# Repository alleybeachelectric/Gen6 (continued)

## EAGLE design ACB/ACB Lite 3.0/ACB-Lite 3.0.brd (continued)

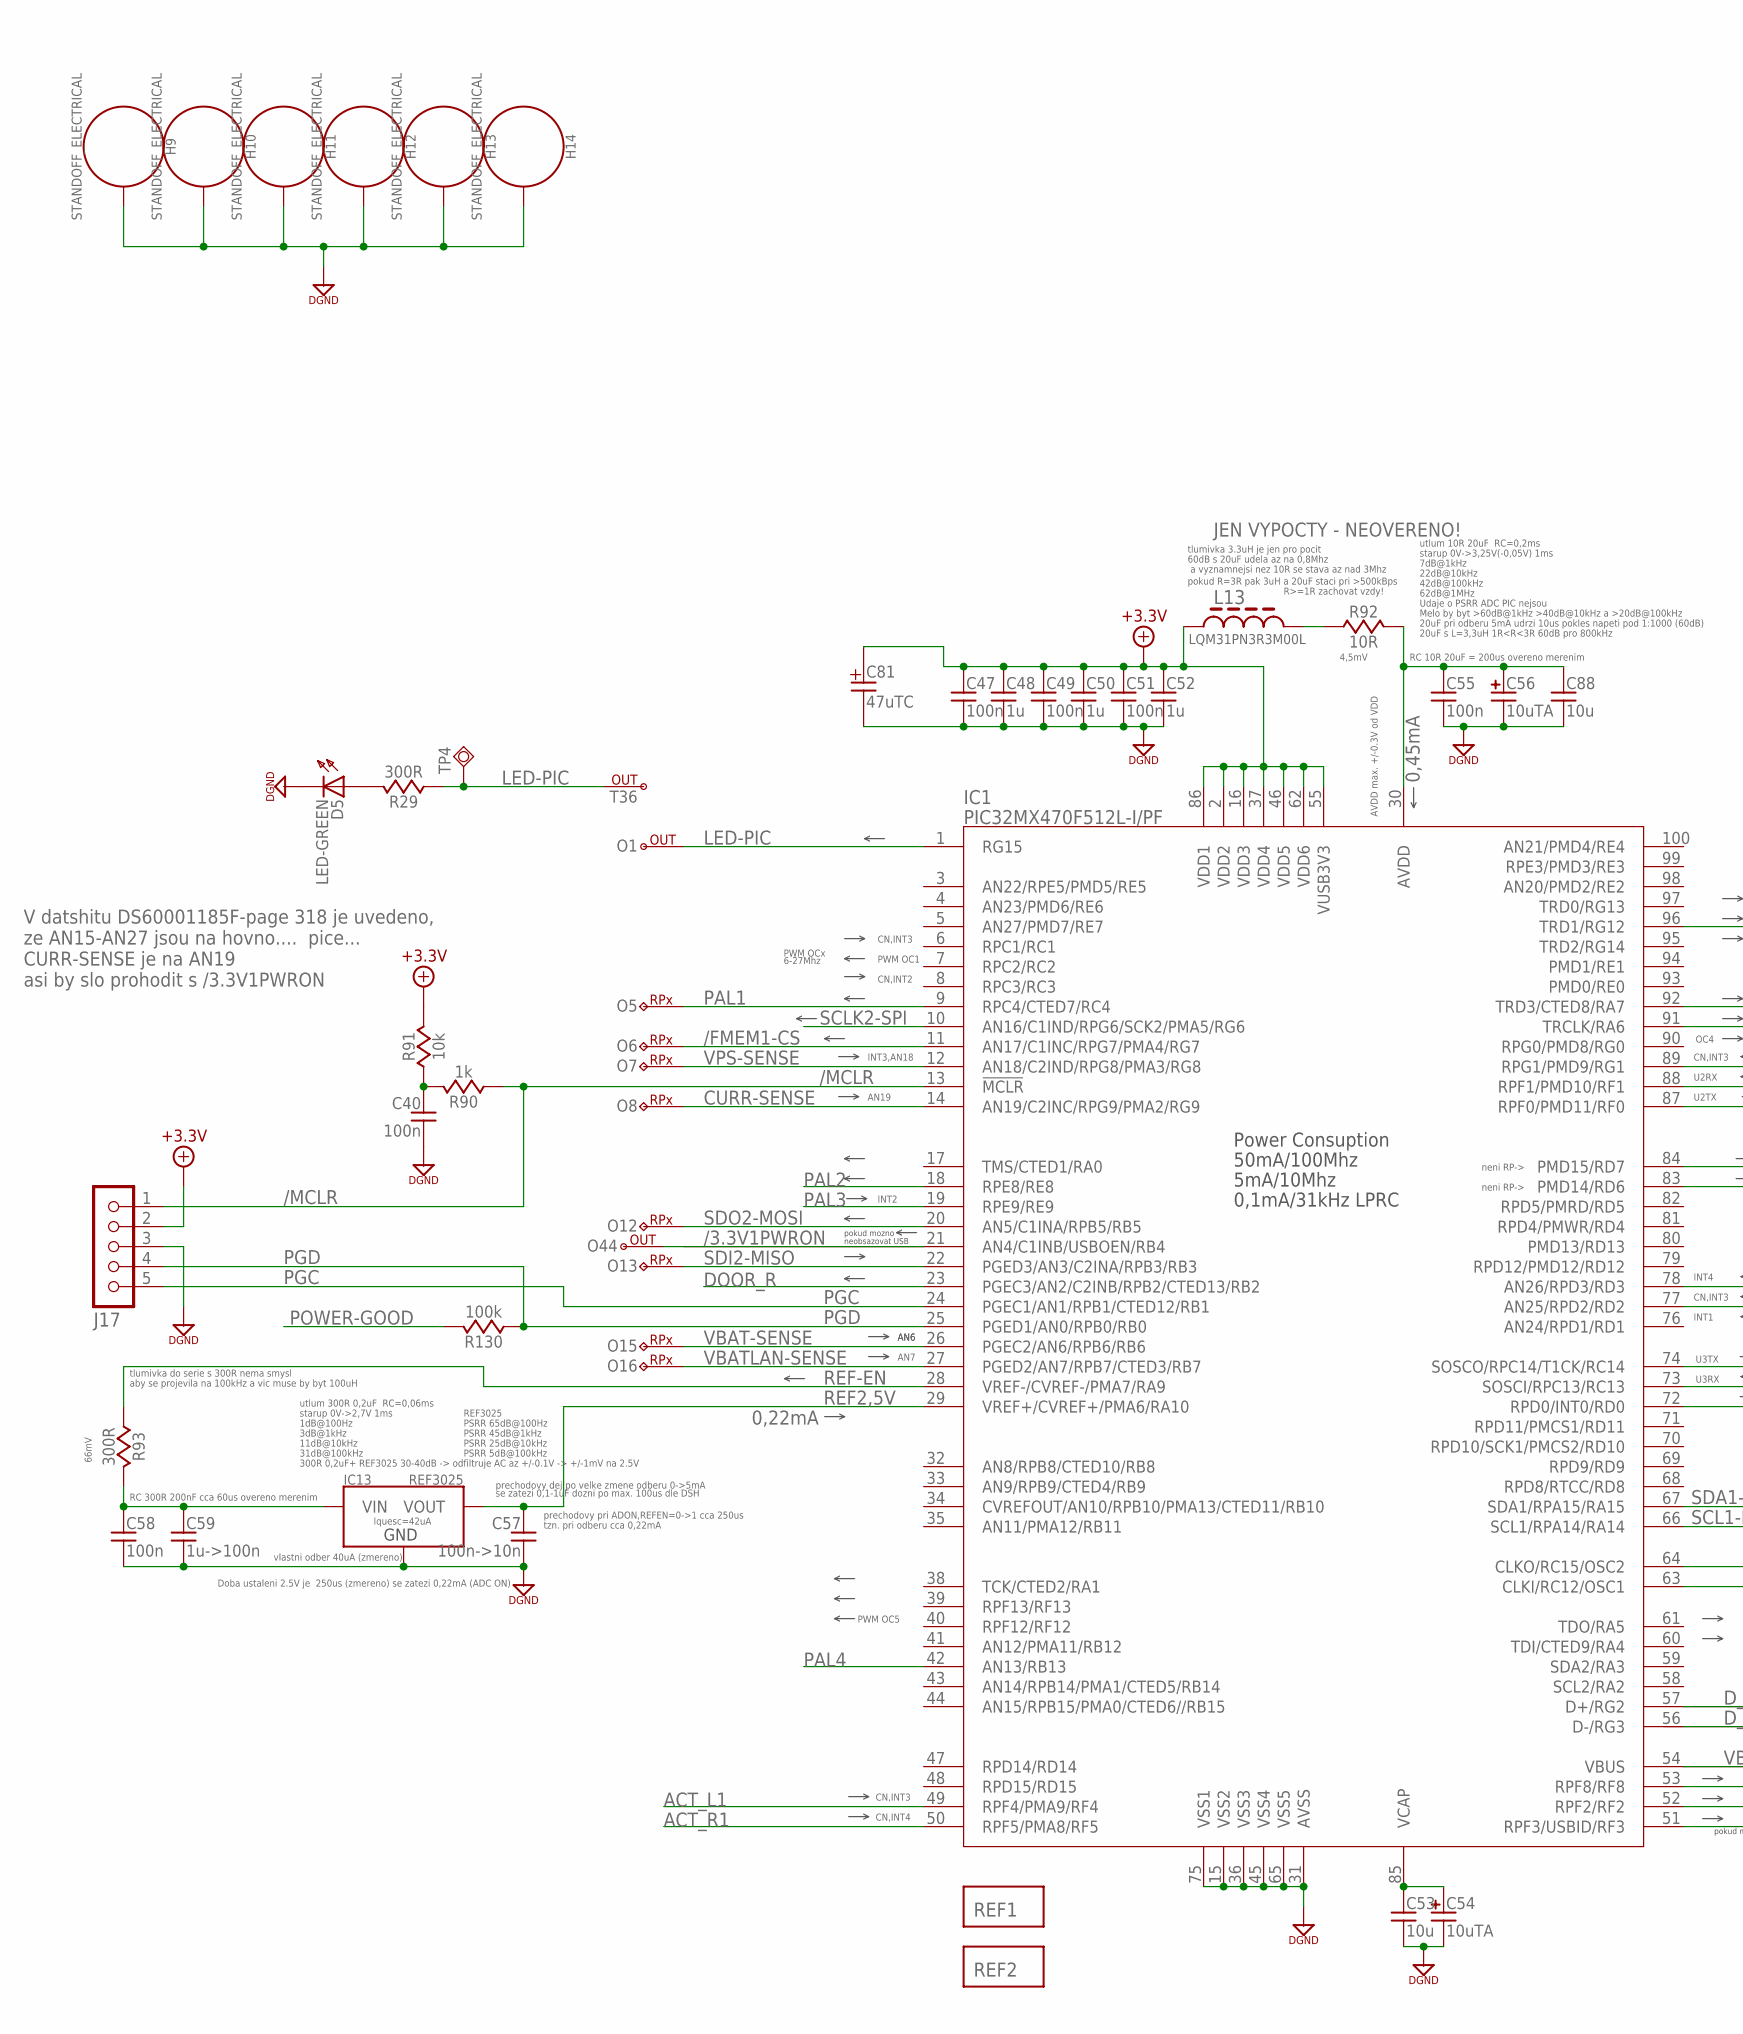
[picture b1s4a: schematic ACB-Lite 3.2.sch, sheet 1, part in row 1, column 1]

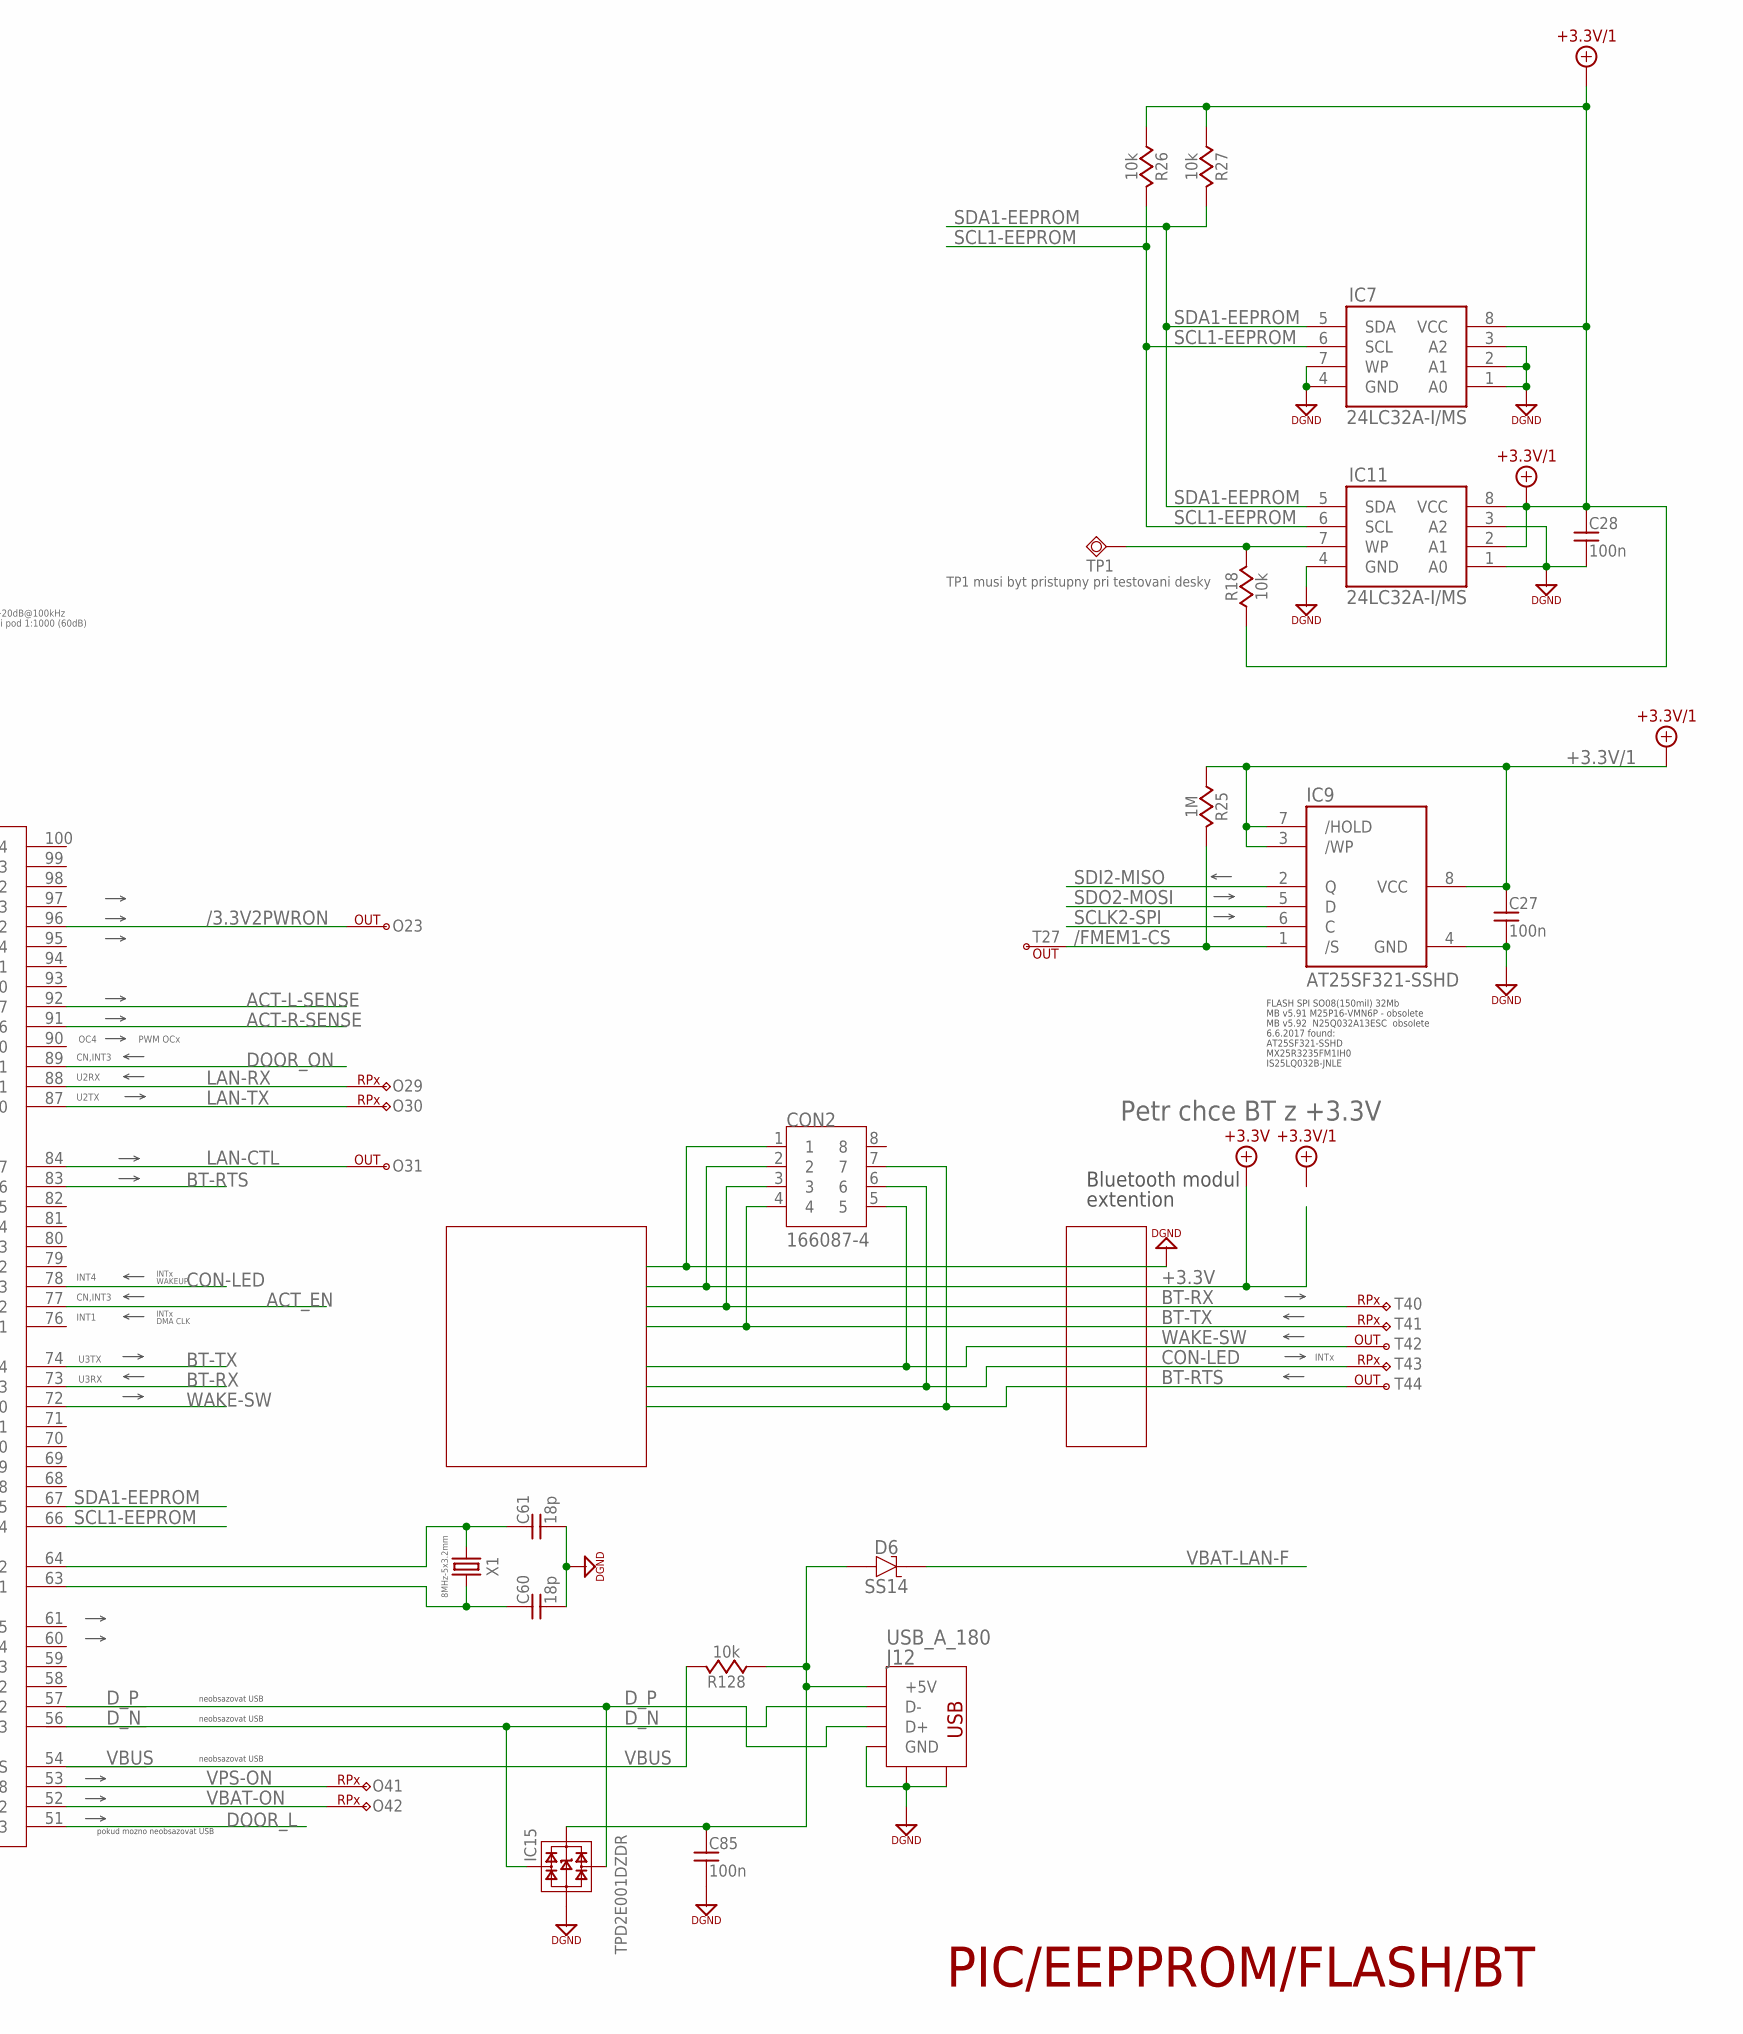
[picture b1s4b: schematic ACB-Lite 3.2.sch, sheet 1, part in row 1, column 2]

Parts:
C27, C28, C40, C47, C49, C51, C55, C58, C85: 100n; 0603
C48, C50, C52: 1u; 0603
C53, C88: 10u; 0603
C54, C56: 10uTA; 1206-POL-C
C57: 100n->10n; 0603
C59: 1u->100n; 0603
C60, C61: 18p; 0603
C81: 47uTC; CT-C
CON2: 166087-4
D5: LED-GREEN; 0805-POL-D
D6: SS14; SMA
H9, H10, H11, H12, H13, H14: STANDOFF_ELECTRICAL; STANDOFF-ELECTRICAL
IC1: PIC32MX470F512L-I/PF; TQFP100_14X14_0,5MM
IC7, IC11: 24LC32A-I/MS; MSOP-08
IC9: AT25SF321-SSHD; SO-08
IC13: REF3025; SOT23
IC15: TPD2E001DZDR; SOT-143
J12: USB_A_180; USB_B_180
J17: DNP-open-hole; MA05-1
L13: LQM31PN3R3M00L; 1206
O1, O23, O31, O44: PIC-OUT; TEMP-PAD
O5, O6, O7, O8, O12, O13, O15, O16, O29, O30, O41, O42: PIC-RPX; TEMP-PAD
R18, R26, R27, R91, R128: 10k; 0603
R25: 1M; 0603
R29, R93: 300R; 0603
R90: 1k; 0603
R92: 10R; 0603
R130: 100k; 0603
REF1, REF2: REF
T27, T36, T42, T44: PIC-OUT; TEMP-PAD
T40, T41, T43: PIC-RPX; TEMP-PAD
TP1: DNP-TestPoint; SMD_ROUND_1MM
TP4: DNP-TestPoint; TH_ROUND_14MM08MM
X1: 8MHz-5x3.2mm; 7B

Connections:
+3.3V: C47.1, C48.1, C49.1, C50.1, C51.1, C52.1, C81.+, CON2.2, IC1.2 (VDD2), IC1.16 (VDD3), IC1.37 (VDD4), IC1.46 (VDD5), IC1.55 (VUSB3V3), IC1.62 (VDD6), IC1.86 (VDD1), J17.2, L13.1, R91.2; also elsewhere on the board
+3.3V/1: C27.1, C28.1, IC7.8 (VCC), IC9.3 (/WP), IC9.7 (/HOLD), IC9.8 (VCC), IC11.2 (A1), IC11.8 (VCC), R18.1, R25.2, R26.1, R27.1; also elsewhere on the board
/3.3V1PWRON: IC1.21 (AN4/C1INB/USBOEN/RB4), O44.P$1; also elsewhere on the board
/3.3V2PWRON: IC1.96 (TRD1/RG12), O23.P$1; also elsewhere on the board
/FMEM1-CS: IC1.11 (AN17/C1INC/RPG7/PMA4/RG7), IC9.1 (/S), O6.P$1, R25.1, T27.P$1
/MCLR: IC1.13 (!MCLR), J17.1, R90.2
ACT-L-SENSE: IC1.92 (TRD3/CTED8/RA7); also elsewhere on the board
ACT-R-SENSE: IC1.91 (TRCLK/RA6); also elsewhere on the board
ACT_EN: IC1.77 (AN25/RPD2/RD2); also elsewhere on the board
ACT_L1: IC1.49 (RPF4/PMA9/RF4); also elsewhere on the board
ACT_R1: IC1.50 (RPF5/PMA8/RF5); also elsewhere on the board
AVDD: C55.1, C56.+, C88.1, IC1.30 (AVDD), R92.2
BT-RTS: CON2.7, IC1.83 (PMD14/RD6), T44.P$1; also elsewhere on the board
BT-RX: CON2.3, IC1.73 (SOSCI/RPC13/RC13), T40.P$1; also elsewhere on the board
BT-TX: CON2.4, IC1.74 (SOSCO/RPC14/T1CK/RC14), T41.P$1; also elsewhere on the board
CON-LED: CON2.6, IC1.78 (AN26/RPD3/RD3), T43.P$1; also elsewhere on the board
CURR-SENSE: IC1.14 (AN19/C2INC/RPG9/PMA2/RG9), O8.P$1; also elsewhere on the board
DOOR_L: IC1.51 (RPF3/USBID/RF3); also elsewhere on the board
DOOR_ON: IC1.89 (RPG1/PMD9/RG1); also elsewhere on the board
DOOR_R: IC1.23 (PGEC3/AN2/C2INB/RPB2/CTED13/RB2); also elsewhere on the board
D_N: IC1.56 (D-/RG3), IC15.2, J12.2_D- (D-)
D_P: IC1.57 (D+/RG2), IC15.3, J12.3_D+ (D+)
LAN-CTL: IC1.84 (PMD15/RD7), O31.P$1; also elsewhere on the board
LAN-RX: IC1.88 (RPF1/PMD10/RF1), O29.P$1; also elsewhere on the board
LAN-TX: IC1.87 (RPF0/PMD11/RF0), O30.P$1; also elsewhere on the board
LED-PIC: IC1.1 (RG15), O1.P$1, R29.1, T36.P$1, TP4.P$1
unnamed: IC11.7 (WP), R18.2, TP1.P$1
unnamed: D5.A, R29.2
unnamed: L13.2, R92.1
unnamed: C61.1, IC1.64 (CLKO/RC15/OSC2), X1.1
unnamed: C60.1, IC1.63 (CLKI/RC12/OSC1), X1.3 (2)
unnamed: C58.1, C59.1, IC13.1 (VIN), R93.2
unnamed: C40.1, R90.1, R91.1
unnamed: C85.1, D6.A, IC15.4, J12.1_+5V (+5V), R128.1
PGC: IC1.24 (PGEC1/AN1/RPB1/CTED12/RB1), J17.5
PGD: IC1.25 (PGED1/AN0/RPB0/RB0), J17.4, R130.2
POWER-GOOD: R130.1; also elsewhere on the board
REF2,5V: C57.1, IC1.29 (VREF+/CVREF+/PMA6/RA10), IC13.2 (VOUT)
REF-EN: IC1.28 (VREF-/CVREF-/PMA7/RA9), R93.1
SCL1-EEPROM: IC1.66 (SCL1/RPA14/RA14), IC7.6 (SCL), IC11.6 (SCL), R26.2
SCLK2-SPI: IC1.10 (AN16/C1IND/RPG6/SCK2/PMA5/RG6), IC9.6 (C)
SDA1-EEPROM: IC1.67 (SDA1/RPA15/RA15), IC7.5 (SDA), IC11.5 (SDA), R27.2
SDI2-MISO: IC1.22 (PGED3/AN3/C2INA/RPB3/RB3), IC9.2 (Q), O13.P$1
SDO2-MOSI: IC1.20 (AN5/C1INA/RPB5/RB5), IC9.5 (D), O12.P$1
VBAT-LAN-F: D6.K; also elsewhere on the board
VBAT-ON: IC1.52 (RPF2/RF2), O42.P$1; also elsewhere on the board
VBAT-SENSE: IC1.26 (PGEC2/AN6/RPB6/RB6), O15.P$1; also elsewhere on the board
VBATLAN-SENSE: IC1.27 (PGED2/AN7/RPB7/CTED3/RB7), O16.P$1; also elsewhere on the board
VBUS: IC1.54 (VBUS), R128.2
VCAP: C53.1, C54.+, IC1.85 (VCAP)
VPS-ON: IC1.53 (RPF8/RF8), O41.P$1; also elsewhere on the board
VPS-SENSE: IC1.12 (AN18/C2IND/RPG8/PMA3/RG8), O7.P$1; also elsewhere on the board
WAKE-SW: CON2.5, IC1.72 (RPD0/INT0/RD0), T42.P$1; also elsewhere on the board

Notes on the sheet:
MB v5.91 M25P16-VMN6P - obsolete
MB v5.92 N25Q032A13ESC obsolete
AT25SF321-SSHD
MX25R3235FM1IH0
IS25LQ032B-JNLE
FLASH SPI SO08(150mil) 32Mb
6.6.2017 found:
Power Consuption
50mA/100Mhz
5mA/10Mhz
0,1mA/31kHz LPRC
pokud mozno
TP1 musi byt pristupny pri testovani desky
neobsazovat USB
pokud mozno neobsazovat USB
PWM OCx
6-27Mhz
INTx
DMA CLK
WAKEUP
PSRR 25dB@10kHz
PSRR 65dB@100Hz
PSRR 45dB@1kHz
PSRR 5dB@100kHz
300R 0,2uF+ REF3025 30-40dB -> odfiltruje AC az +/-0.1V -> +/-1mV na 2.5V
REF3025
prechodovy dej po velke zmene odberu 0->5mA
se zatezi 0,1-1uF dozni po max. 100us dle DSH
Iquesc=42uA
tlumivka 3.3uH je jen pro pocit
PWM OC1
INT3,AN18
AN19
CN,INT3
CN,INT2
INT2
PWM OC5
AN6
AN7
CN,INT4

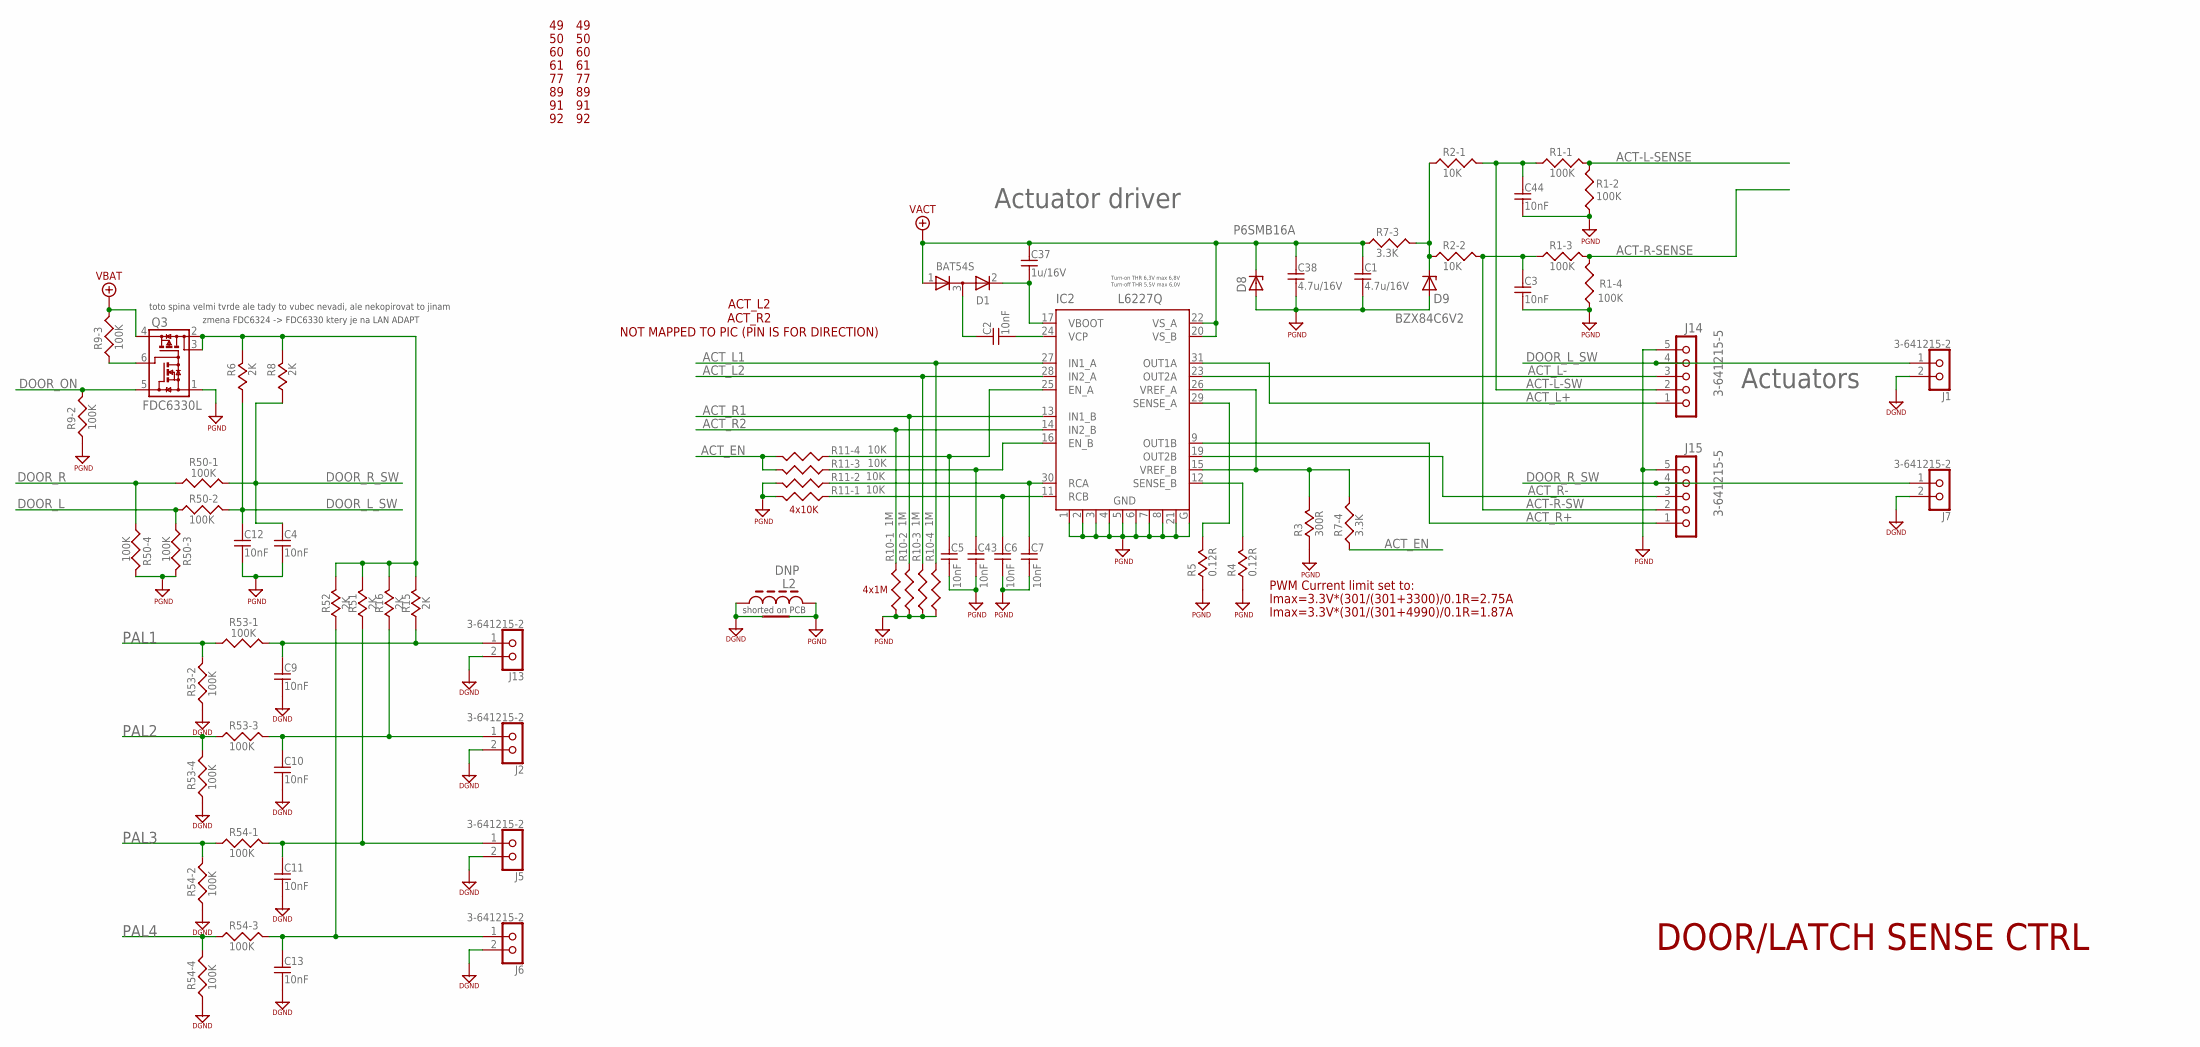
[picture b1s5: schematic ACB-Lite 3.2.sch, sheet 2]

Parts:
C1, C38: 4.7u/16V; 0805
C2, C3, C4, C5, C6, C7, C9, C10, C11, C12, C13, C43, C44: 10nF; 0603
C37: 1u/16V; 0603
D1: BAT54S; SOT-23
D8: P6SMB16A; SMB
D9: BZX84C6V2; SOT-23
IC2: L6227Q; SQFP-S-5X5-32
J1, J2, J5, J6, J7, J13: 3-641215-2
J14, J15: 3-641215-5
L2: DNP; 0805-0RTOP
Q3: FDC6330L; SSOT-6
R1, R9, R50, R53, R54: 100K; 0603-ARRAY
R2, R11: 10K; 0603-ARRAY
R3: 300R; 0603
R4, R5: 0.12R; 0805
R6, R8, R15, R16, R51, R52: 2K; 0603
R7: 3.3K; 0603-ARRAY
R10: 1M; 0603-ARRAY

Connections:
ACT-L-SENSE: R1.7 (2), R1.8 (2); also elsewhere on the board
ACT-R-SENSE: R1.5 (2), R1.6 (2); also elsewhere on the board
ACT_EN: R7.4 (1), R11.5 (2), R11.6 (2); also elsewhere on the board
ACT_L1: IC2.27 (IN1_A), R10.5 (2); also elsewhere on the board
ACT_L2: IC2.28 (IN2_A), R10.6 (2)
ACT_L+: IC2.31 (OUT1A), J14.1; also elsewhere on the board
ACT_L-: IC2.23 (OUT2A), J14.3; also elsewhere on the board
ACT_R1: IC2.13 (IN1_B), R10.7 (2); also elsewhere on the board
ACT_R2: IC2.14 (IN2_B), R10.8 (2)
ACT_R+: IC2.9 (OUT1B), J15.1; also elsewhere on the board
ACT_R-: IC2.19 (OUT2B), J15.3; also elsewhere on the board
DOOR_L: R50.2 (1), R50.3 (1); also elsewhere on the board
DOOR_L_SW: C12.1, J1.1, J14.4, R6.2, R50.7 (2); also elsewhere on the board
DOOR_ON: Q3.5 (Q1G), R9.7 (2); also elsewhere on the board
DOOR_R: R50.1, R50.4 (1); also elsewhere on the board
DOOR_R_SW: C4.1, J7.1, J15.4, R8.2, R50.8 (2); also elsewhere on the board
unnamed: C5.1, IC2.25 (EN_A), R11.4 (1)
unnamed: C43.1, IC2.16 (EN_B), R11.3 (1)
unnamed: C6.1, IC2.11 (RCB), R11.1
unnamed: C2.2, IC2.24 (VCP)
unnamed: C2.1, D1.3 (KA)
unnamed: IC2.12 (SENSE_B), R4.2
unnamed: Q3.6 (Q2G), R9.3 (1)
unnamed: IC2.29 (SENSE_A), R5.2
unnamed: C37.2, D1.2 (K), IC2.17 (VBOOT)
unnamed: C7.1, IC2.30 (RCA), R11.2 (1)
unnamed: IC2.15 (VREF_B), IC2.26 (VREF_A), R3.2, R7.5 (2)
unnamed: R53.1, R53.7 (2)
unnamed: R53.3 (1), R53.5 (2)
unnamed: R54.1, R54.7 (2)
unnamed: R54.3 (1), R54.5 (2)

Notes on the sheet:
Actuator driver
Actuators
4x10K
4x1M
PWM Current limit set to:
Imax=3.3V*(301/(301+3300)/0.1R=2.75A
Imax=3.3V*(301/(301+4990)/0.1R=1.87A
Turn-on THR 6,3V max 6,8V
Turn-off THR 5,5V max 6,0V
toto spina velmi tvrde ale tady to vubec nevadi, ale nekopirovat to jinam
zmena FDC6324 -> FDC6330 ktery je na LAN ADAPT
shorted on PCB
DOOR/LATCH SENSE CTRL
ACT_L2 ACT_R2 NOT MAPPED TO PIC (PIN IS FOR DIRECTION)

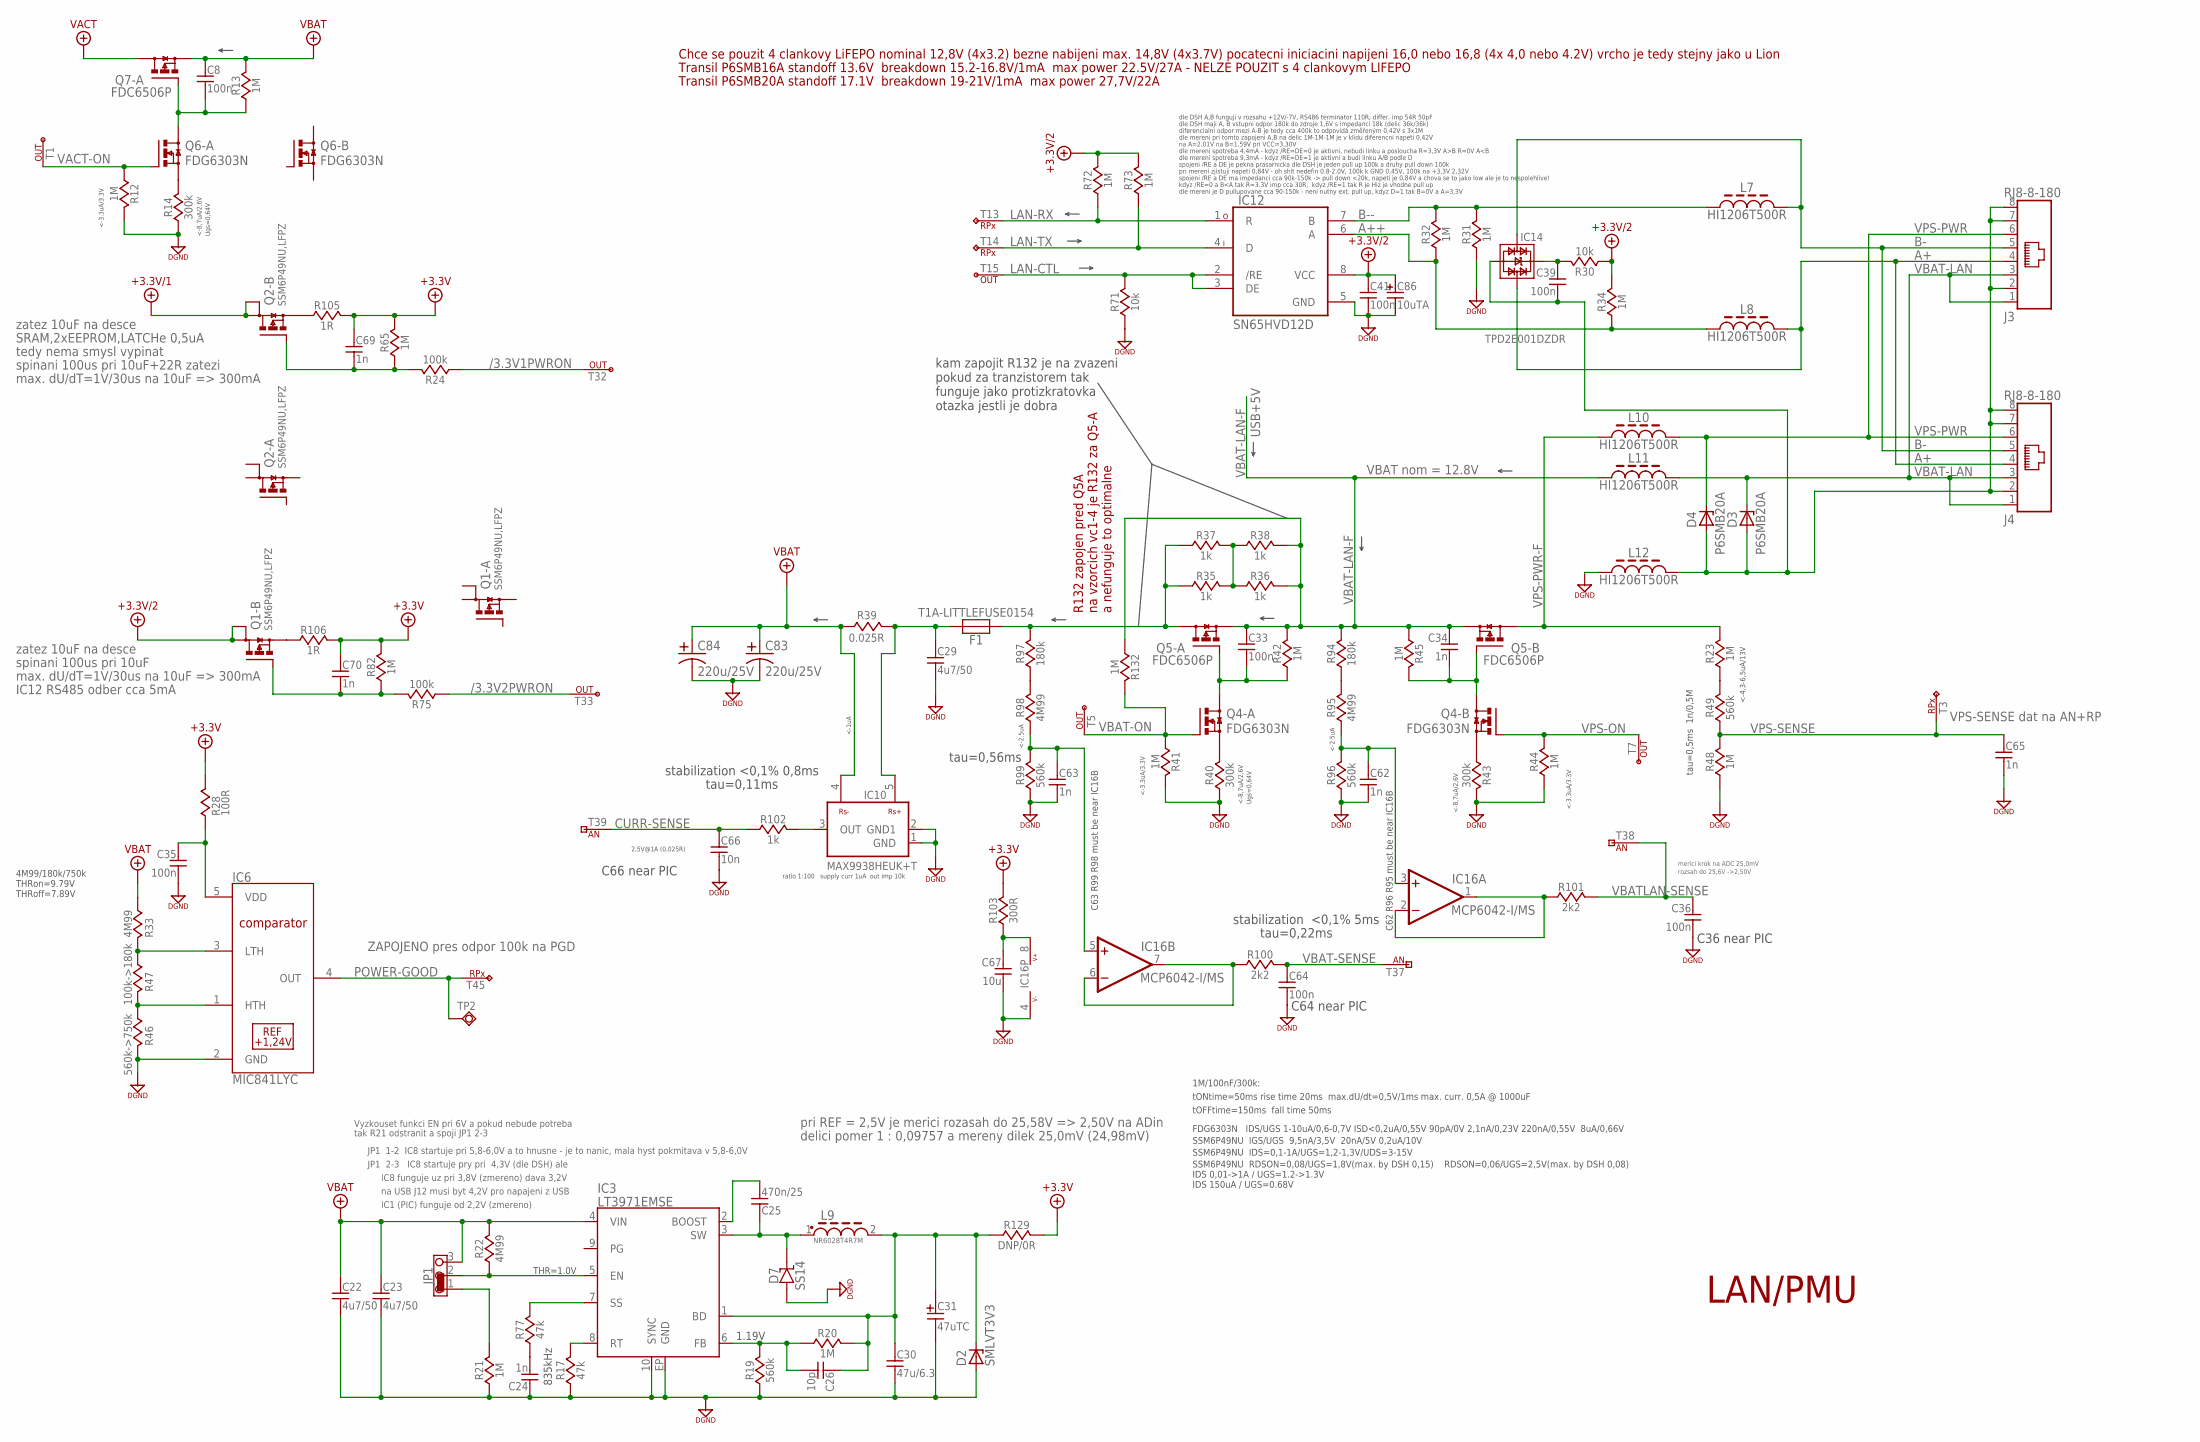
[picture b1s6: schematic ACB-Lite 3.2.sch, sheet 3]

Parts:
C8, C33, C35, C36, C39, C41, C64: 100n; 0603
C22, C23, C29: 4u7/50; 1206
C24, C34, C62, C63, C65, C69, C70: 1n; 0603
C25: 470n/25; 0603
C26: 10p; 0603
C30: 47u/6.3; 1206
C31: 47uTC; CT-C
C66: 10n; 0603
C67: 10u; 0603
C83, C84: 220u/25V; CAP_8MM_DIA_SMT
C86: 10uTA; 1206-POL-C
D2: SMLVT3V3; SMA
D3, D4: P6SMB20A; SMB
D7: SS14; SMA
F1: T1A-LITTLEFUSE0154; LITTLEFUSE0154
IC3: LT3971EMSE; MSOP10EXP
IC6: MIC841LYC; SC-70-5
IC10: MAX9938HEUK+T; SOT23-5
IC12: SN65HVD12D; SO08
IC14: TPD2E001DZDR; SOT-143
IC16: MCP6042-I/MS; MSOP-08
J3, J4: RJ8-8-180
JP1: JP3CLOSE12
L7, L8, L10, L11, L12: HI1206T500R; 1206
L9: NR6028T4R7M; NR6028
Q1, Q2: SSM6P49NU,LFPZ; MICRO_FET
Q4, Q6: FDG6303N; SC70-6
Q5, Q7: FDC6506P; SSOT-6
R12, R13, R20, R21, R23, R31, R32, R34, R41, R42, R44, R45, R48, R65, R72, R73, R82, R132: 1M; 0603
R14, R40, R43: 300k; 0603
R17, R77: 47k; 0603
R19, R49, R96, R99: 560k; 0603
R22, R33, R95, R98: 4M99; 0603
R24, R75: 100k; 0603
R28: 100R; 0603
R30, R71: 10k; 0603
R35, R36, R37, R38: 1k; 0805
R39: 0.025R; 0805
R46: 560k->750k; 0603
R47: 100k->180k; 0603
R94, R97: 180k; 0603
R100, R101: 2k2; 0603
R102: 1k; 0603
R103: 300R; 0603
R105, R106: 1R; 0805
R129: DNP/0R; 0603
T1, T5, T7, T15, T32, T33: PIC-OUT; TEMP-PAD
T3, T13, T14, T45: PIC-RPX; TEMP-PAD
T37, T38, T39: PIN-AN; TEMP-PAD
TP2: DNP-TestPoint; TH_ROUND_14MM08MM

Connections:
+3,3V-FILT: C35.1, IC6.5 (VDD), R28.1
+3.3V: C69.1, C70.1, R28.2, R65.1, R82.1, R103.2, R105.2, R106.2, R129.1; also elsewhere on the board
+3.3V/1: Q2.3 (D), Q2.P2 (D1); also elsewhere on the board
+3.3V/2: C41.1, C86.+, IC12.8 (VCC), Q1.3 (D), Q1.P2 (D1), R30.2, R34.1, R72.1, R73.2
/3.3V1PWRON: R24.2, T32.P$1; also elsewhere on the board
/3.3V2PWRON: R75.2, T33.P$1; also elsewhere on the board
A+: IC14.3, J3.4, J4.4, L8.2
A++: IC12.6 (A), L8.1, R32.2, R34.2
B-: IC14.2, J3.5, J4.5, L7.2
B--: IC12.7 (B), L7.1, R31.1, R32.1
CURR-SENSE: C66.1, R102.2, T39.P$1; also elsewhere on the board
DGND-F: C39.2, D3.A, D4.A, IC14.1, J3.2, J3.7, J3.8, J4.2, J4.7, J4.8, L12.2
GATE-Q12A: C33.2, Q4.6 (D), Q5.1 (G), R42.2
GATE-Q12A1: C8.2, Q6.6 (D), Q7.1 (G), R13.2
GATE-Q12B: C34.2, Q4.3 (D), Q5.3 (G), R45.2
LAN-CTL: IC12.2 (/RE), IC12.3 (DE), R71.1, T15.P$1; also elsewhere on the board
LAN-RX: IC12.1 (R), R72.2, T13.P$1; also elsewhere on the board
LAN-TX: IC12.4 (D), R73.1, T14.P$1; also elsewhere on the board
unnamed: Q6.1 (S), R14.2
unnamed: Q4.1 (S), R40.2
unnamed: Q4.4 (S), R43.2
unnamed: C39.1, IC14.4, R30.1
unnamed: R35.2, R36.1, R37.2, R38.1
unnamed: C29.1, F1.1, IC10.5 (VIN+), R39.2
unnamed: IC6.1 (HTH), R46.2, R47.1
unnamed: IC6.3 (LTH), R33.1, R47.2
unnamed: Q1.4 (S), R106.1
unnamed: F1.2, Q5.6 (D), R35.1, R37.1, R97.1
unnamed: R94.2, R95.1
unnamed: C62.1, IC16.3 (+IN), R95.2, R96.1
unnamed: C26.2, IC3.6 (FB), R19.1, R20.2
unnamed: C24.2, R77.2
unnamed: C25.1, D7.K, IC3.3 (SW), L9.1
unnamed: IC3.8 (RT), R17.1
unnamed: IC3.7 (SS), R77.1
unnamed: IC3.5 (EN), JP1.2, R22.2
unnamed: Q2.4 (S), R105.1
unnamed: C25.2, IC3.2 (BOOST)
unnamed: R97.2, R98.1
unnamed: R23.1, R49.2
unnamed: C63.1, IC16.5 (+IN), R98.2, R99.1
unnamed: IC16.6 (-IN), IC16.7 (OUT), R100.2
unnamed: C67.1, IC16.8 (V+), R103.1
unnamed: IC16.1 (OUT), IC16.2 (-IN), R101.2
unnamed: C69.2, Q2.5 (G), R24.1, R65.2
unnamed: IC10.3 (OUT), R102.1
unnamed: C70.2, Q1.5 (G), R75.1, R82.2
unnamed: JP1.1, R21.1
OUT+3.3V: C26.1, C30.1, C31.+, D2.+ (C), IC3.1 (BD), L9.2, R20.1, R129.2
POWER-GOOD: IC6.4 (OUT), T45.P$1, TP2.P$1; also elsewhere on the board
VACT-ON: Q6.2 (G), R12.1, T1.P$1
VBAT-LAN: D3.C, J3.1, J3.3, J4.1, J4.3, L11.2
VBAT-LAN-F: C33.1, C34.1, L11.1, Q5.2 (S), Q5.5 (S), R36.2, R38.2, R42.1, R45.1, R94.1, R132.1; also elsewhere on the board
VBAT-ON: Q4.2 (G), R41.1, R132.2, T5.P$1; also elsewhere on the board
VBAT-SENSE: C64.1, R100.1, T37.P$1; also elsewhere on the board
VBATLAN-SENSE: C36.1, R101.1, T38.P$1; also elsewhere on the board
VPS-ON: Q4.5 (G), R44.1, T7.P$1; also elsewhere on the board
VPS-PWR: D4.C, J3.6, J4.6, L10.2
VPS-PWR-F: L10.1, Q5.4 (D), R23.2
VPS-SENSE: C65.1, R48.2, R49.1, T3.P$1; also elsewhere on the board

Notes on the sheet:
<-8,7uA/2,6V
Ugs=0,64V
<-4,3-6,5uA/13V
<-3.3uA/3.3V
tau=0,5ms 1n/0,5M
Chce se pouzit 4 clankovy LiFEPO nominal 12,8V (4x3.2) bezne nabijeni max. 14,8V (4x3.7V) pocatecni iniciacini napijeni 16,0 nebo 16,8 (4x 4,0 nebo 4.2V) vrcho je tedy stejny jako u Lion
Transil P6SMB16A standoff 13.6V breakdown 15.2-16.8V/1mA max power 22.5V/27A - NELZE POUZIT s 4 clankovym LIFEPO
Transil P6SMB20A standoff 17.1V breakdown 19-21V/1mA max power 27,7V/22A
FDG6303N IDS/UGS 1-10uA/0,6-0,7V ISD<0,2uA/0,55V 90pA/0V 2,1nA/0,23V 220nA/0,55V 8uA/0,66V
SSM6P49NU IGS/UGS 9,5nA/3,5V 20nA/5V 0,2uA/10V
SSM6P49NU IDS=0,1-1A/UGS=1,2-1,3V/UDS=3-15V
SSM6P49NU RDSON=0,08/UGS=1,8V(max. by DSH 0,15) RDSON=0,06/UGS=2,5V(max. by DSH 0,08)
tONtime=50ms rise time 20ms max.dU/dt=0,5V/1ms max. curr. 0,5A @ 1000uF
tOFFtime=150ms fall time 50ms
1M/100nF/300k:
IDS 150uA / UGS=0.68V
IDS 0,01->1A / UGS=1.2->1.3V
ratio 1:100 supply curr 1uA out imp 10k
2,5V@1A (0,025R)
VBAT nom = 12.8V
diferencialni odpor mezi A-B je tedy cca 400k to odpovídá změřeným 0,42V s 3x1M
dle mereni spotreba 4,4mA - kdyz /RE=DE=0 je aktivni, nebudi linku a posloucha R=3,3V A>B R=0V A<B
dle mereni pri tomto zapojeni A,B na delic 1M-1M-1M je v klidu diferencni napeti 0,42V
spojeni /RE a DE ma impedanci cca 90k-150k -> pull down <20k, napeti je 0,84V a chova se to jako low ale je to nespolehlive!
spojeni /RE a DE je pekna prasarnicka dle DSH je jeden pull up 100k a druhy pull down 100k
dle mereni spotreba 9,3mA - kdyz /RE=DE=1 je aktivni a budi linku A/B podle D
pri mereni zjistuji napeti 0,84V - oh shit nedefin 0.8-2.0V, 100k k GND 0,45V, 100k na +3,3V 2,32V
dle mereni je D pullupovane cca 90-150k - neni nutny ext. pull up, kdyz D=1 tak B=0V a A=3,3V
kdyz /RE=0 a B<A tak R=3.3V imp cca 30R, kdyz /RE=1 tak R je Hiz je vhodne pull up
dle DSH maji A, B vstupni odpor 180k do zdroje 1,6V s impedanci 18k (delic 36k/36k)
na A=2,01V na B=1,59V pri VCC=3,30V
835kHz
1.19V
THR=1.0V
dle DSH A,B funguji v rozsahu +12V/-7V, RS486 terminator 110R, differ. imp 54R 50pF
tau=0,22ms
tau=0,56ms
stabilization <0,1% 5ms
tau=0,11ms
stabilization <0,1% 0,8ms

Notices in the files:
ACB/ACB Lite 3.0/ACB-Lite 3.0.brd:
(C) 2017 eLock Technologies LCC
parts and their libraries:
SparkFun-Hardware: Licensing: Creative Commons ShareAlike 4.0 International - https://creativecommons.org/licenses/by-sa/4.0
